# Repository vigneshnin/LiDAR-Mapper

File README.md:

# LiDAR-Mapper
A LiDAR 3D Mapping system which is very low cost at 5000₹(~80$) made using arduino.
The PCB is there in the LA3DMS folder. There are some errors in the pcb but it can be fixed by using jumpers.
You'll need an extra power supply for the servo motors (if you use mg995, smaller servo will work fine) because the one on the pcb is not powerful enough.
Use an arduino or FTDI programmer for the UART communication to transfer co-ordinate data to PC.
Use the .pde file with processing IDE to visualise the data.

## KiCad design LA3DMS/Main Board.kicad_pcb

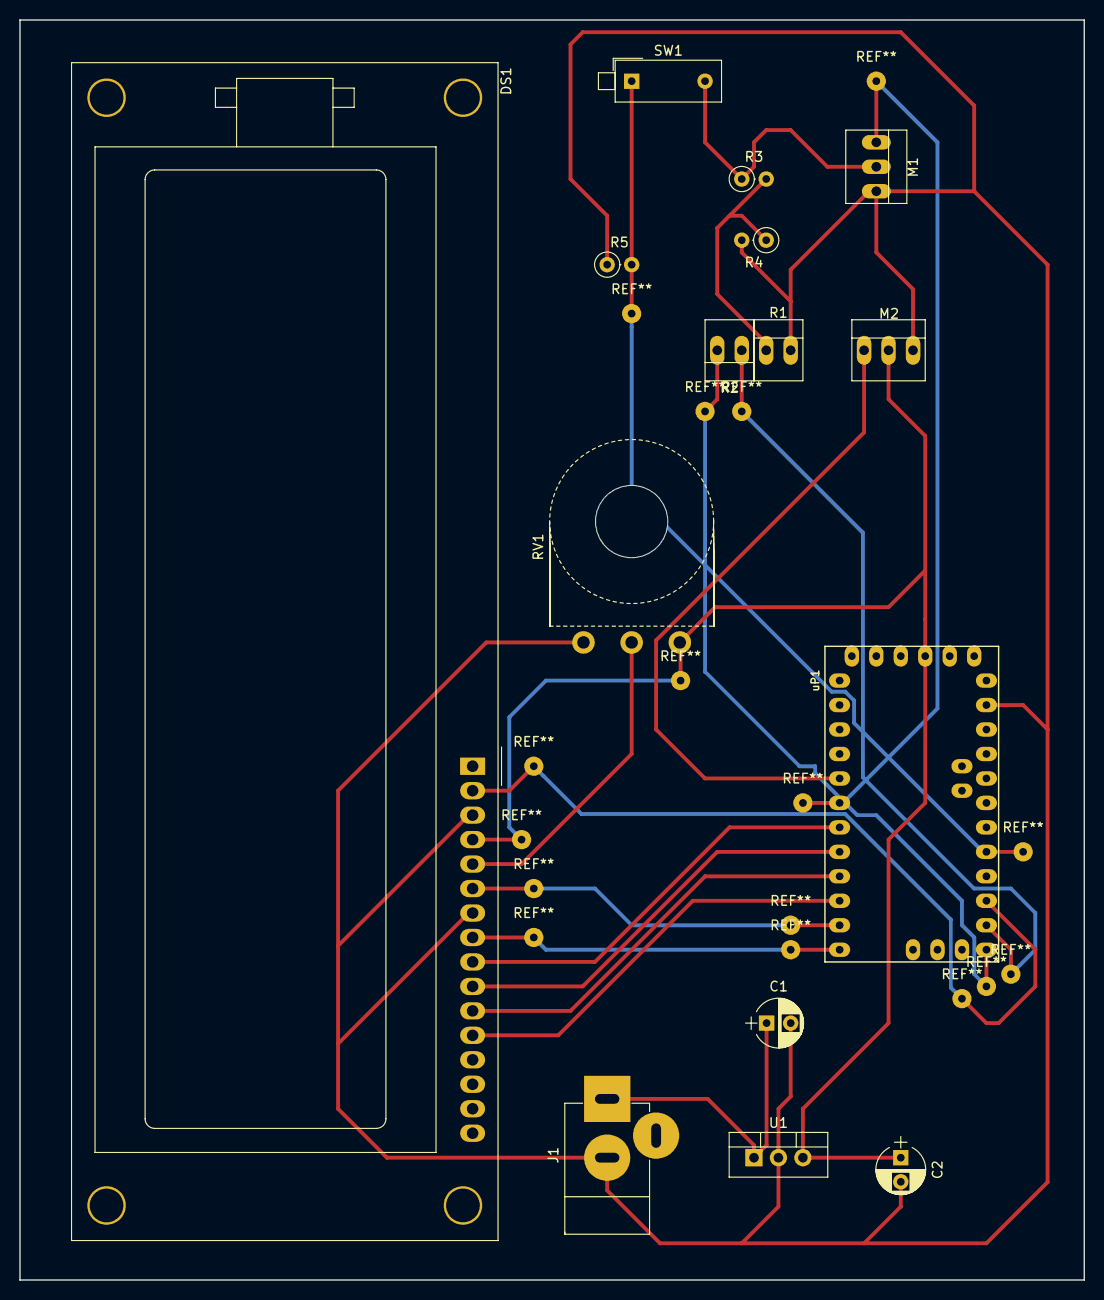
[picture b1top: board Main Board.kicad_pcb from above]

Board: 2 copper layers, 110.5 x 130.8 mm, 15 parts (0 on the bottom side), 10 nets.

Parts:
C1, C2: CP; CP_Radial_D5.0mm_P2.50mm
DS1: HY1602E
J1: Barrel_Jack; JACK_ALIM
M1, M2: Motor_Servo; PINHEAD1-3
R1, R2: R; PINHEAD1-2
R3, R4, R5: R; R_Axial_DIN0207_L6.3mm_D2.5mm_P2.54mm_Vertical
RV1: POT; Potentiometer_Omeg_PC16PU_Horizontal_MountLS
SW1: SW_Push; SW_DIP_x1_W7.62mm_Piano
U1: L7805; TO-220-3_Vertical
uP1: ARDUPROMINI; pro_mini

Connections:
GND: C1.2, C2.2, DS1.3, DS1.7, J1.2, M1.3, M2.3, R1.2, R4.2, R5.1, RV1.3, U1.2, uP1.23
unnamed: C1.1, J1.1, U1.1
unnamed: C2.1, M1.2, M2.2, R3.1, SW1.2, U1.3, uP1.31
unnamed: DS1.5, RV1.2
unnamed: DS1.9, uP1.7
unnamed: DS1.10, uP1.8
unnamed: DS1.11, uP1.9
unnamed: DS1.12, uP1.10
unnamed: M2.1, uP1.5
unnamed: R1.1, R3.2, R4.1

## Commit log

2018-04-03 Add files via upload
    This .pde file should be used with processing IDE to visualize the 3D point cloud
2018-04-03 Update LA3DMS.ino
    This is the Arduino code to be programmed to the arduino pro mini (I used this but any arduino will do).
2018-04-03 Add files via upload
    The video shows its working and the image shows its hardware.
